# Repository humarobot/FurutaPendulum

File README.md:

# FurutaPendulum

旋转倒立摆

视频在这https://www.bilibili.com/video/BV1Wh411U76g/

## 模型

- 使用UG画的
  - 为什么不用solidworks？因为UG可以在没有独立显卡的笔记本流畅运行，也不用一直换新版本，而且稳定性不知道高到哪里去了

## 电路

- 编码器的板子是用Kicad画的，驱动是用AltiumDesigner17画的
  - 为什么不都用AD？因为我现在主用Kicad
  - 为什么不都用Kicad？因为想重温一下AD(我的电脑用18版之后的卡卡的，气抖冷！)

## 代码

- 使用的是STM32duino和SimpleFOC
  - 为什么不用keil或是stm32cubemx？因为SimpleFOC太香了，没有它就没有这个项目
  - 为什么要用STM32而不是328p？希望算的快一点，控制频率高一点(它再涨价我以后就用国产芯片了。摔！)

## 理论

- 请见Ben Katz大佬的[博客](https://build-its.blogspot.com/2019/12/furuta-pendulums.html)
- 看不懂也没关系，等我有空了写写教程

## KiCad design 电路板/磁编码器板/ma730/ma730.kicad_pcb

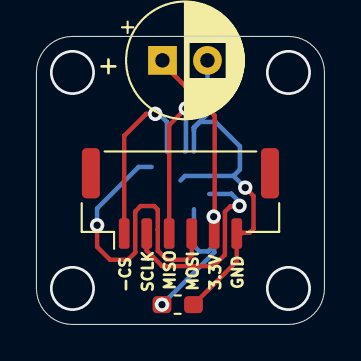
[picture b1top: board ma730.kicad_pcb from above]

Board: 2 copper layers, 16.0 x 16.0 mm, 4 parts (1 on the bottom side), 6 nets.

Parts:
+: CP; CP_Radial_D6.3mm_P2.50mm
C1: 1uF; C_0603_1608Metric_Pad1.05x0.95mm_HandSolder
J2: Conn_01x06_Female; JST_GH_BM06B-GHS-TBT_1x06-1MP_P1.25mm_Vertical
U1: MA730; QFN-16-1EP_3x3mm_P0.5mm_EP1.45x1.45mm

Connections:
+3V3: +.1, C1.1, J2.5, U1.13
GND: +.2, C1.2, J2.6, U1.8, U1.10, U1.17
unnamed: J2.1, U1.5
unnamed: J2.2, U1.12
unnamed: J2.3, U1.7
unnamed: J2.4, U1.4

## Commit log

2021-04-12 电路 模型 代码
